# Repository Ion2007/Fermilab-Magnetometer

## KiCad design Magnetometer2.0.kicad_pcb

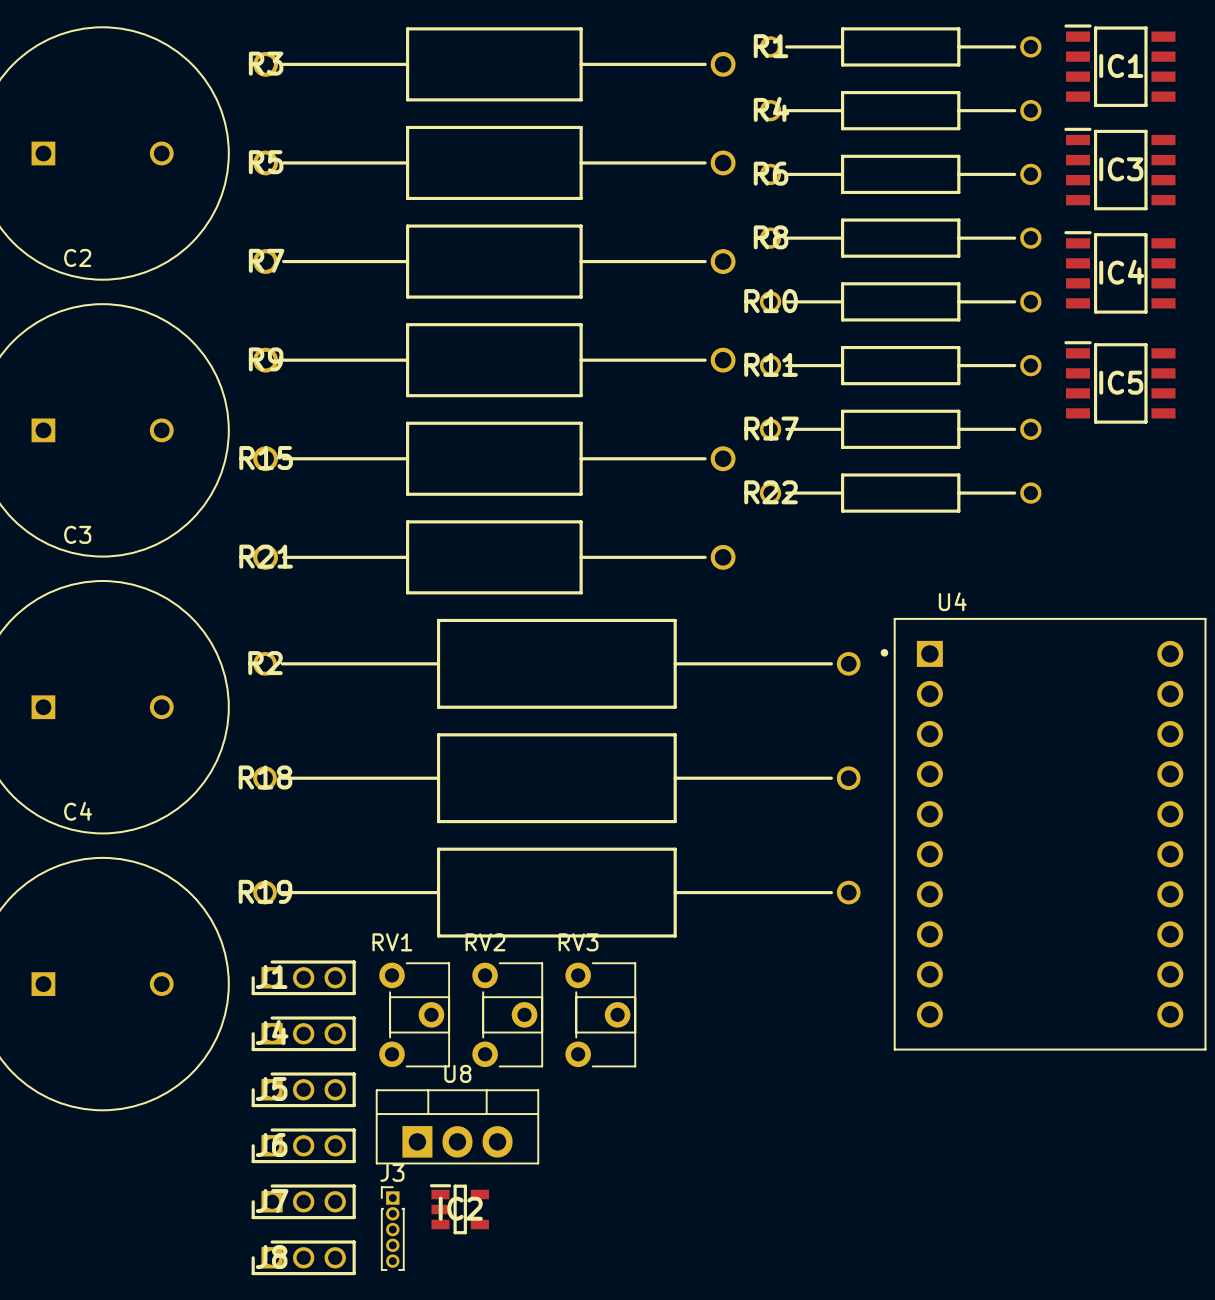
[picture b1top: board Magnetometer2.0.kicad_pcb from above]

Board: 2 copper layers, 38 parts (0 on the bottom side), 30 nets, no tracks yet.

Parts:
C1, C2, C3, C4: C_Polarized; CAPRRD750W80D1600H4150
IC1, IC3, IC4, IC5: TL971ID; SOIC127P600X175-8N
IC2: LK112M25TR; SOT95P280X145-5N
J1, J4, J5, J6, J7, J8: 2355182-3; HDRV3W50P0X200_1X3_600X200X550P
J3: Conn_01x05_Pin; PinHeader_1x05_P1.00mm_Vertical
R1, R4, R6, R8, R10, R11, R17, R22: 5K; RESAD1653W69L737D229
R2, R18, R19: ROX3SJ33R; RESAD3700W80L1500D550
R3, R5, R7, R9, R15, R21: 1kOhm; RESAD2900W85L1100D450
RV1, RV2, RV3: R_Potentiometer; Potentiometer_ACP_CA6-H2,5_Horizontal
U4: HMC2003; DIPS1524W64P254L2730H902Q20
U8: LM7810_TO220; TO-220-3_Vertical

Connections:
+2V5: R3.1, R7.1, R15.1
+10V: IC3.7 (VCC+), IC4.7 (VCC+), IC5.7 (VCC+), J1.1, J5.1, J7.1, R1.1, U8.3 (VO)
+12V: J3.5, U4.10 (V+), U8.1 (VI)
-10V: IC1.6 (OUT), IC3.4 (VCC-), IC4.4 (VCC-), IC5.4 (VCC-), J1.3, J5.3, J7.3, R11.2
GND: IC1.2 (IN-), IC2.2 (GND), J3.4, J4.1, J6.1, J8.1, R4.2, R8.2, R22.2, U4.2 (XOFF-), U4.5 (YOFF-), U4.9 (GND), U4.19 (ZOFF-), U8.2 (GND)
unnamed: IC1.3 (IN+), R1.2, R11.1
unnamed: IC3.3 (IN+), R17.1, R21.2
unnamed: IC3.2 (IN-), R15.2, R22.1
unnamed: IC3.6 (OUT), J3.1, R17.2
unnamed: IC4.3 (IN+), R5.2, R6.1
unnamed: IC4.2 (IN-), R3.2, R4.1
unnamed: IC4.6 (OUT), J3.2, R6.2
unnamed: IC5.3 (IN+), R9.2, R10.1
unnamed: IC5.2 (IN-), R7.2, R8.1
unnamed: IC5.6 (OUT), J3.3, R10.2
unnamed: J1.2, R18.1
unnamed: J4.2, R18.2
unnamed: J4.3, RV1.2
unnamed: J5.2, R19.1
unnamed: J6.2, R19.2
unnamed: J6.3, RV2.2
unnamed: J7.2, R2.1
unnamed: J8.2, R2.2
unnamed: J8.3, RV3.2
unnamed: RV1.3, U4.18 (XOFF+)
unnamed: R9.1, U4.7 (XOUT)
unnamed: RV2.3, U4.16 (YOFF+)
unnamed: R5.1, U4.14 (YOUT)
unnamed: RV3.3, U4.20 (ZOFF+)
unnamed: R21.1, U4.6 (ZOUT)

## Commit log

2024-11-05 files
